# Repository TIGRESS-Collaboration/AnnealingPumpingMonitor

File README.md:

# AnnealingPumpingMonitor
Contains code and PCD designs and documentation regarding the remote monitor station for HPGe detector annealing and pumping.

In PAMonitor_Interface_Board you'll find the Eagle CAD design files for the PCB. 

In RaspberryPi_Code you'll find the home directory of the webserver which contains all the code necessary to run the monitor system.

Some notes:
1) The UUGear library included here must be used, there were some lines of code which needed to be commented out to tame excessive messages to the system logs.
2) readData.c is deprecated. Use readData.cpp
3) Same as above for build.sh and buildcpp.sh, respectively.
4) runMonitorStn.sh was to be a script that could be launched to do all work and checks necessary to ensure the monitor station would run, however, there are still some bugs to be ironed out.

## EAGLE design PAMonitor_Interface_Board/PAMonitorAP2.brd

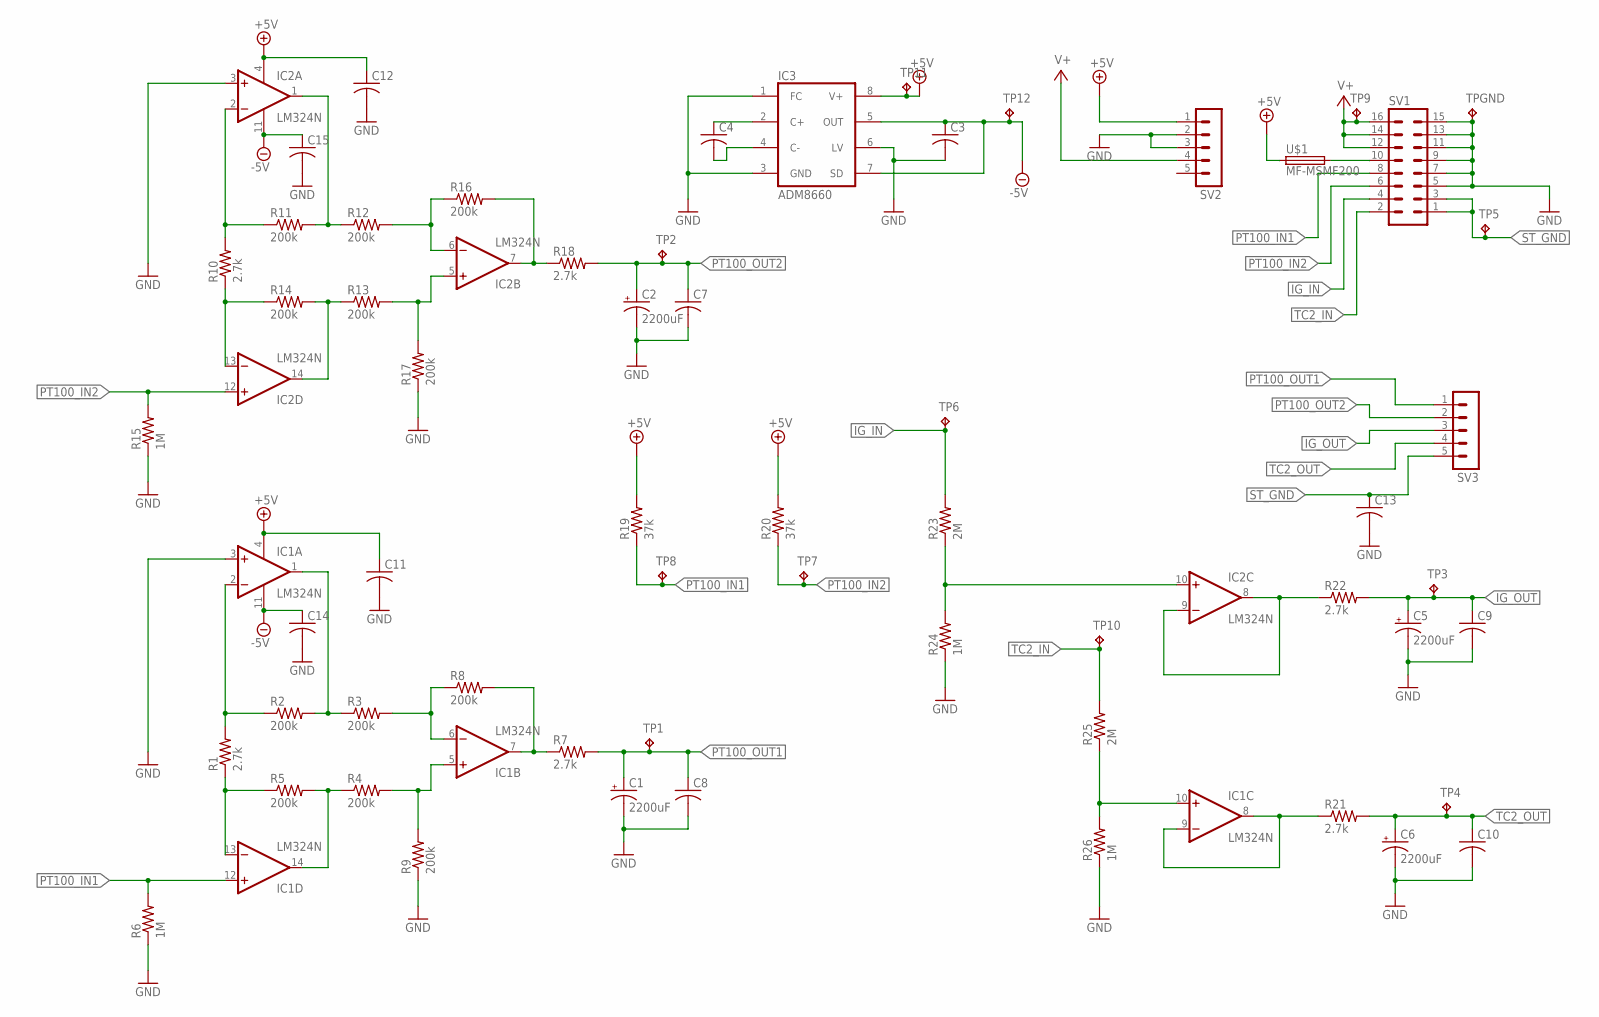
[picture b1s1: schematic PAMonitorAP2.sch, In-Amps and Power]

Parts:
C1, C2, C5, C6: 2200uF; E5-10,5
C3, C4, C7, C8, C9, C10, C11, C12, C13, C14, C15: C-US025-025X050; C025-025X050
IC1, IC2: LM324N; DIL14
IC3: ADM8660; ADM8660-DIL08
R1, R7, R10, R18, R21, R22: 2.7k; 0309/12
R2, R3, R4, R5, R8, R9, R11, R12, R13, R14, R16, R17: 200k; 0309/12
R6, R15, R24, R26: 1M; 0309/12
R19, R20: 37k; 0309/12
R23, R25: 2M; 0309/12
SV1: MA08-2
SV2, SV3: MA05-1
TP1, TP2, TP3, TP4, TP5, TP6, TP7, TP8, TP9, TP10, TP11, TP12: TPB2,54; B2,54
TPGND: TPB2,54; B2,54
U$1: MF-MSMF200

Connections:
+5V: C11.1, C12.1, IC1.4 (V+), IC2.4 (V+), IC3.8 (V+), R19.2, R20.2, SV2.1, TP11.TP, U$1.1
-5V: C3.1, C14.1, C15.1, IC1.11 (V-), IC2.11 (V-), IC3.5 (OUT), IC3.7 (SD), TP12.TP
GND: C1.-, C2.-, C3.2, C5.-, C6.-, C7.2, C8.2, C9.2, C10.2, C11.2, C12.2, C13.2, C14.2, C15.2, IC1.3 (+IN), IC2.3 (+IN), IC3.1 (FC), IC3.3 (GND), IC3.6 (LV), R6.1, R9.1, R15.1, R17.1, R24.1, R26.1, SV1.5, SV1.7, SV1.9, SV1.11, SV1.13, SV1.15, SV2.2, SV2.3, TPGND.TP
IG_IN: R23.2, SV1.4, TP6.TP
IG_OUT: C5.+, C9.1, R22.2, SV3.3, TP3.TP
unnamed: IC1.13 (-IN), R1.1, R5.1
unnamed: IC1.2 (-IN), R1.2, R2.1
unnamed: IC1.1 (OUT), R2.2, R3.1
unnamed: IC1.6 (-IN), R3.2, R8.1
unnamed: IC1.5 (+IN), R4.2, R9.2
unnamed: IC1.14 (OUT), R4.1, R5.2
unnamed: IC1.7 (OUT), R7.1, R8.2
unnamed: IC2.13 (-IN), R10.1, R14.1
unnamed: IC2.2 (-IN), R10.2, R11.1
unnamed: IC2.1 (OUT), R11.2, R12.1
unnamed: IC2.6 (-IN), R12.2, R16.1
unnamed: IC2.5 (+IN), R13.2, R17.2
unnamed: IC2.14 (OUT), R13.1, R14.2
unnamed: IC2.7 (OUT), R16.2, R18.1
unnamed: C4.1, IC3.2 (C+)
unnamed: C4.2, IC3.4 (C-)
unnamed: SV1.10, U$1.2
unnamed: IC2.8 (OUT), IC2.9 (-IN), R22.1
unnamed: IC1.8 (OUT), IC1.9 (-IN), R21.1
unnamed: IC1.10 (+IN), R25.1, R26.2
unnamed: IC2.10 (+IN), R23.1, R24.2
PT100_IN1: IC1.12 (+IN), R6.2, R19.1, SV1.8, TP8.TP
PT100_IN2: IC2.12 (+IN), R15.2, R20.1, SV1.6, TP7.TP
PT100_OUT1: C1.+, C8.1, R7.2, SV3.1, TP1.TP
PT100_OUT2: C2.+, C7.1, R18.2, SV3.2, TP2.TP
ST_GND: C13.1, SV1.1, SV1.3, SV3.5, TP5.TP
TC2_IN: R25.2, SV1.2, TP10.TP
TC2_OUT: C6.+, C10.1, R21.2, SV3.4, TP4.TP
V+: SV1.12, SV1.14, SV1.16, SV2.4, TP9.TP

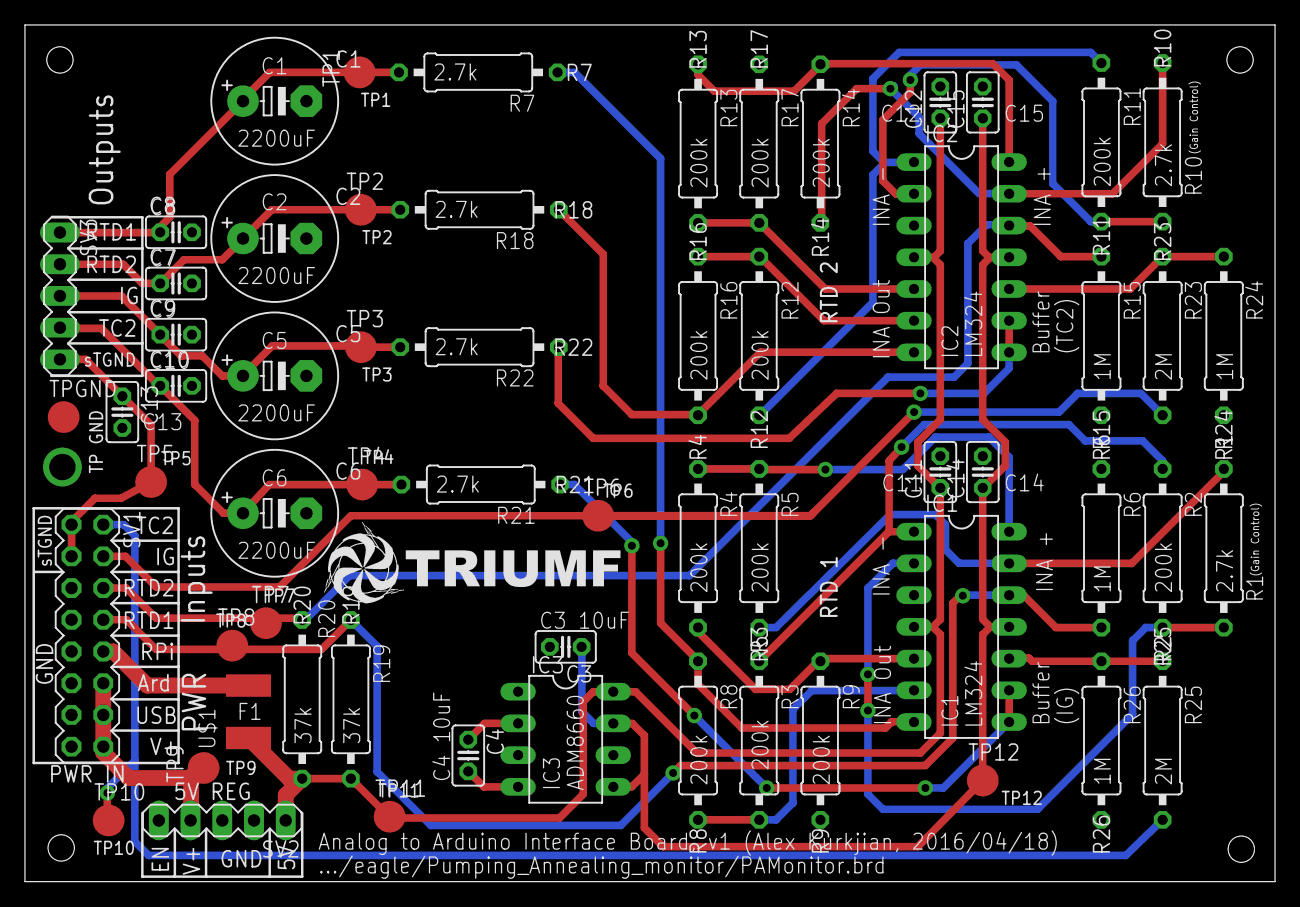
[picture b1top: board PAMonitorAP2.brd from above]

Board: 2 copper layers, 100.1 x 68.6 mm, 61 parts (0 on the bottom side), 34 nets.

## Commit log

2016-08-27 PCB Design Files
    Uploaded board design files for the monitor station.
2016-08-27 Raspberry Pi Code Upload
    Raspberry Pi code used to run the monitor system. Note: Some
    modifications to the UUGear code were necessary to ensure the Raspberry
    Pi system logs wouldn't not become completely flooded and fill the
    filesystem with excess information.
    A few other things:
    - readData.C is deprecated, use readData.cpp
